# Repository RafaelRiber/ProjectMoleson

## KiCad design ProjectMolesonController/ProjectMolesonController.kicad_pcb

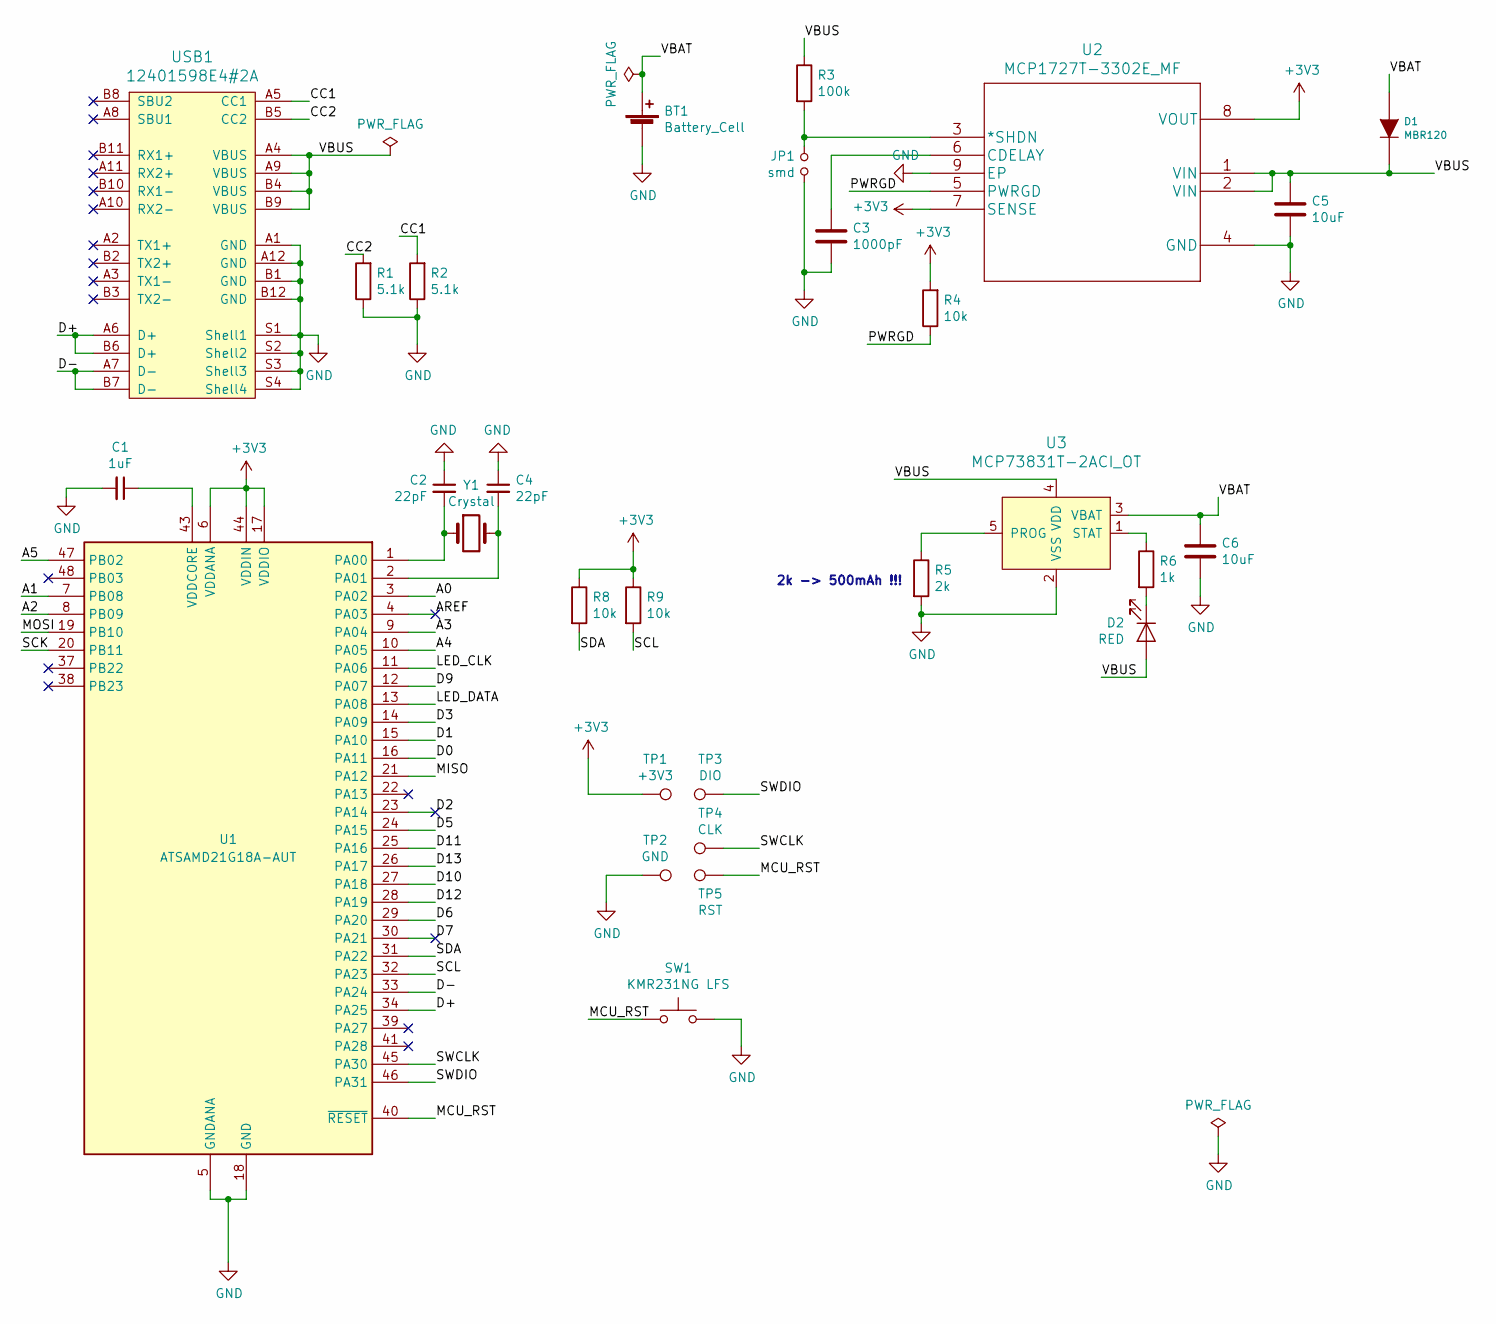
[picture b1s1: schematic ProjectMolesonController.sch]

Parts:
BT1: Battery_Cell; JST_PH_S2B-PH-SM4-TB_1x02-1MP_P2.00mm_Horizontal
C1: 1uF; C_0402_1005Metric
C2, C4: 22pF; C_0402_1005Metric
C3: 1000pF; C_0402_1005Metric
C5, C6: 10uF; C_0402_1005Metric
D1: MBR120; D_SOD-123F
D2: RED; LED_0805_2012Metric
JP1: smd; SolderJumper-2_P1.3mm_Open_RoundedPad1.0x1.5mm
R1, R2: 5.1k; R_0402_1005Metric
R3: 100k; R_0402_1005Metric
R4, R8, R9: 10k; R_0402_1005Metric
R5: 2k; R_0402_1005Metric
R6: 1k; R_0402_1005Metric
SW1: KMR231NG LFS; SW_Push_1P1T_NO_CK_KMR2
TP1: +3V3; TestPoint_Pad_D4.0mm
TP2: GND; TestPoint_Pad_D4.0mm
TP3: DIO; TestPoint_Pad_D4.0mm
TP4: CLK; TestPoint_Pad_D4.0mm
TP5: RST; TestPoint_Pad_D4.0mm
U1: ATSAMD21G18A-AUT; QFN50P700X700X90-49N
U2: MCP1727T-3302E_MF; DFN-8-1EP_3x3mm_P0.5mm_EP1.66x2.38mm
U3: MCP73831T-2ACI_OT; SOT-753; MPN MCP73831T-2ACI/OT; Digi-Key_PN MCP73831T-2ACI/OTCT-ND
USB1: 12401598E4#2A
Y1: Crystal; Crystal_SMD_3215-2Pin_3.2x1.5mm

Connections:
+3V3: R4.2, R8.1, R9.1, TP1.1, U1.6 (VDDANA), U1.17 (VDDIO), U1.36 (VDDIO), U1.44 (VDDIN), U2.7 (SENSE), U2.8 (VOUT)
/A0: U1.3 (PA02)
/A1: U1.7 (PB08)
/A2: U1.8 (PB09)
/A3: U1.9 (PA04)
/A4: U1.10 (PA05)
/A5: U1.47 (PB02)
/AREF: U1.4 (PA03)
/CC1: R2.2, USB1.A5 (CC1)
/CC2: R1.2, USB1.B5 (CC2)
/D0: U1.16 (PA11)
/D1: U1.15 (PA10)
/D2: U1.23 (PA14)
/D3: U1.14 (PA09)
/D5: U1.24 (PA15)
/D6: U1.29 (PA20)
/D7: U1.30 (PA21)
/D9: U1.12 (PA07)
/D10: U1.27 (PA18)
/D11: U1.25 (PA16)
/D12: U1.28 (PA19)
/D13: U1.26 (PA17)
/D+: U1.34 (PA25), USB1.A6 (D+), USB1.B6 (D+)
/D-: U1.33 (PA24), USB1.A7 (D-), USB1.B7 (D-)
/LED_CLK: U1.11 (PA06)
/LED_DATA: U1.13 (PA08)
/MCU_RST: SW1.1, TP5.1, U1.40 (~RESET)
/MISO: U1.21 (PA12)
/MOSI: U1.19 (PB10)
/PWRGD: R4.1, U2.5 (PWRGD)
/SCK: U1.20 (PB11)
/SCL: R9.2, U1.32 (PA23)
/SDA: R8.2, U1.31 (PA22)
/SWCLK: TP4.1, U1.45 (PA30)
/SWDIO: TP3.1, U1.46 (PA31)
/VBAT: BT1.1 (+), C6.1, D1.A, U3.3 (VBAT)
/VBUS: C5.1, D1.K, D2.2 (A), R3.1, U2.1 (VIN), U2.2 (VIN), U3.4 (VDD), USB1.A4 (VBUS), USB1.A9 (VBUS), USB1.B4 (VBUS), USB1.B9 (VBUS)
GND: BT1.2 (-), C1.2, C2.1, C3.2, C4.1, C5.2, C6.2, JP1.1, R1.1, R2.1, R5.2, SW1.2, TP2.1, U1.5 (GNDANA), U1.18 (GND), U1.35 (GND), U1.42 (GND), U2.4 (GND), U2.9 (EP), U3.2 (VSS), USB1.A1 (GND), USB1.A12 (GND), USB1.B1 (GND), USB1.B12 (GND), USB1.S1 (Shell1), USB1.S2 (Shell2), USB1.S3 (Shell3), USB1.S4 (Shell4)
unnamed: C1.1, U1.43 (VDDCORE)
unnamed: C2.2, U1.1 (PA00), Y1.1
unnamed: C3.1, U2.6 (CDELAY)
unnamed: C4.2, U1.2 (PA01), Y1.2
unnamed: D2.1 (K), R6.2
unnamed: JP1.2, R3.2, U2.3 (*SHDN)
unnamed: R5.1, U3.5 (PROG)
unnamed: R6.1, U3.1 (STAT)

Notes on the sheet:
2k -> 500mAh !!!

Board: 2 copper layers, 29 parts (0 on the bottom side), 22 nets, no tracks yet.

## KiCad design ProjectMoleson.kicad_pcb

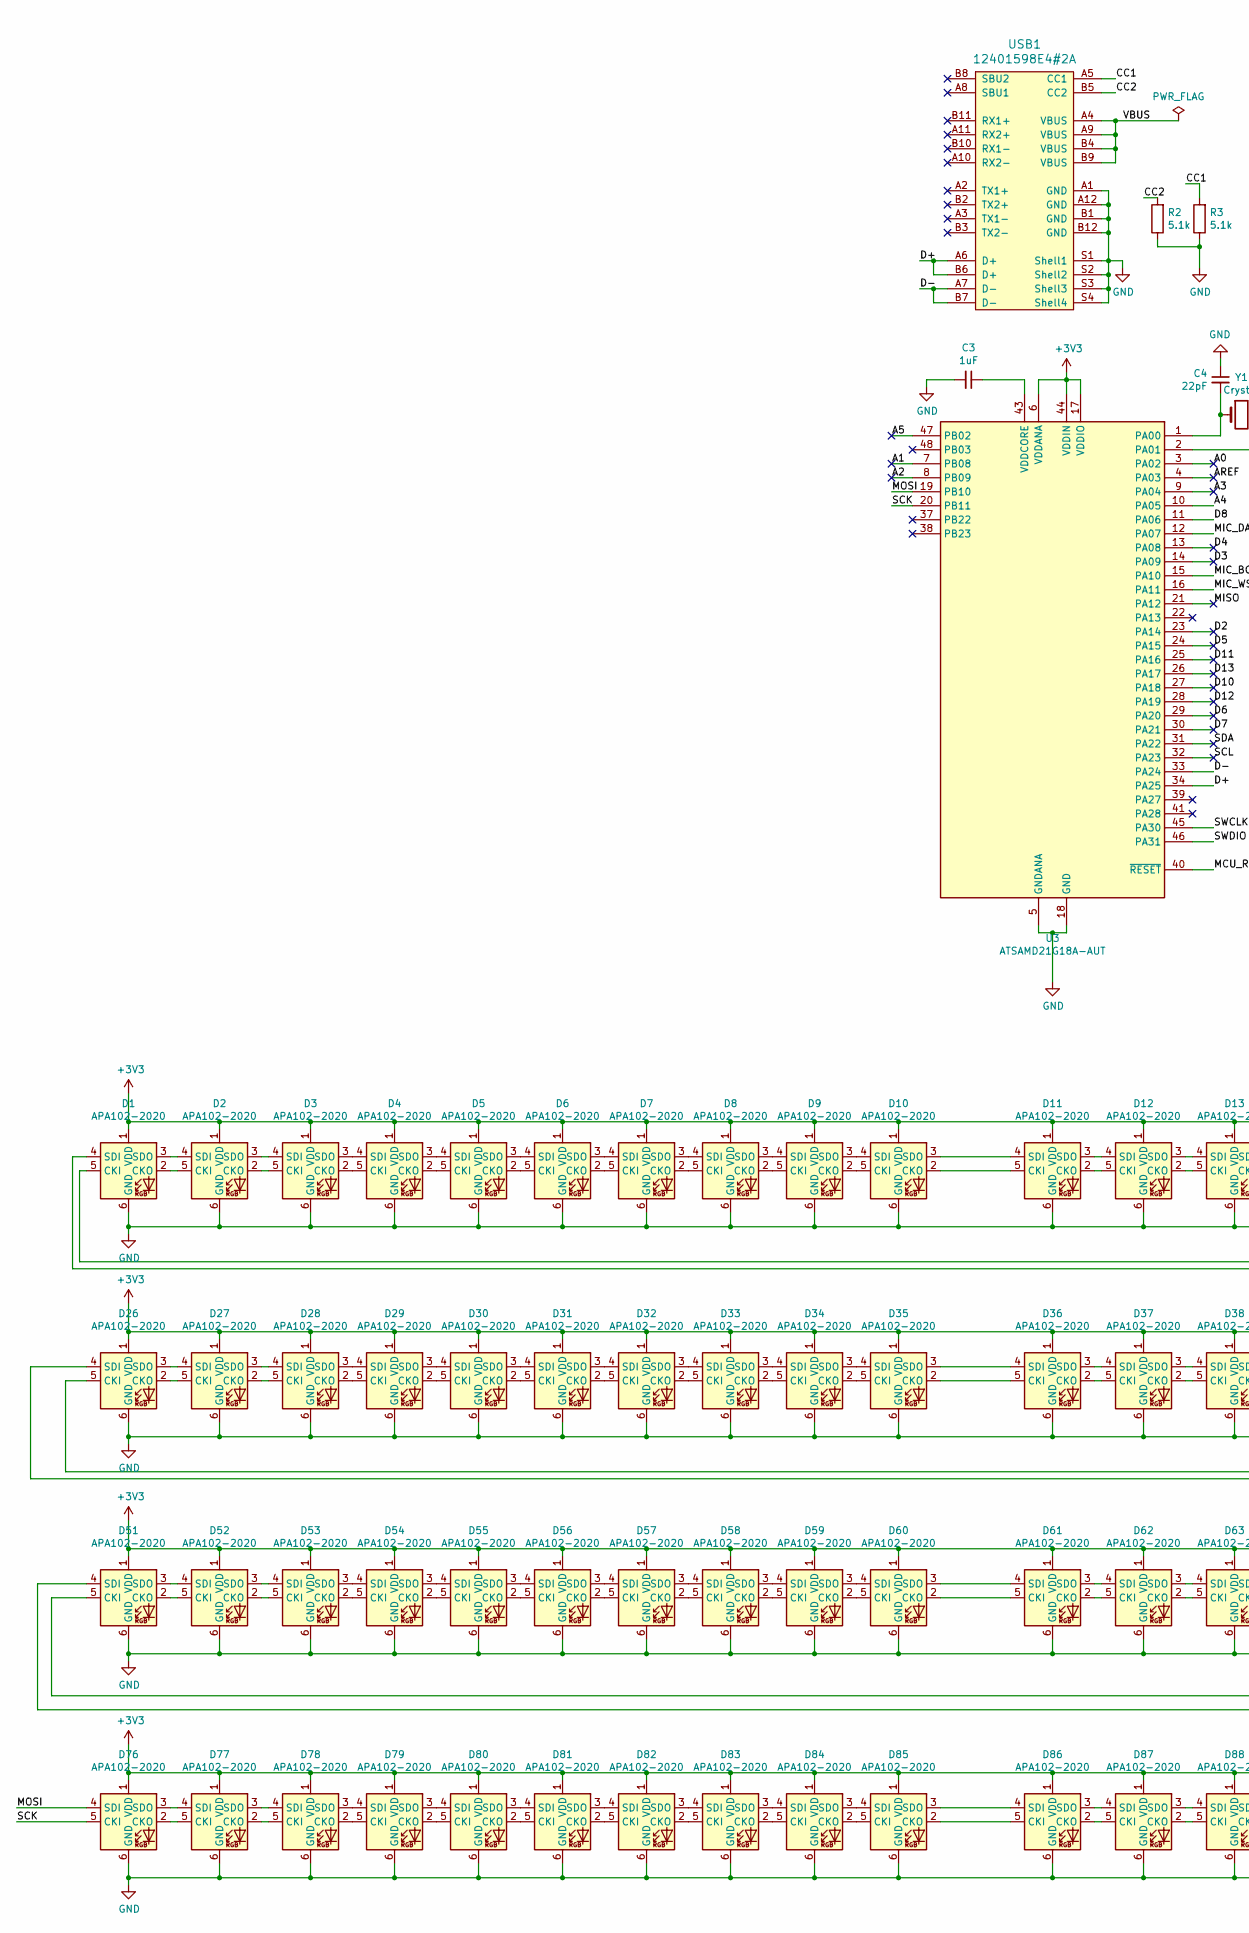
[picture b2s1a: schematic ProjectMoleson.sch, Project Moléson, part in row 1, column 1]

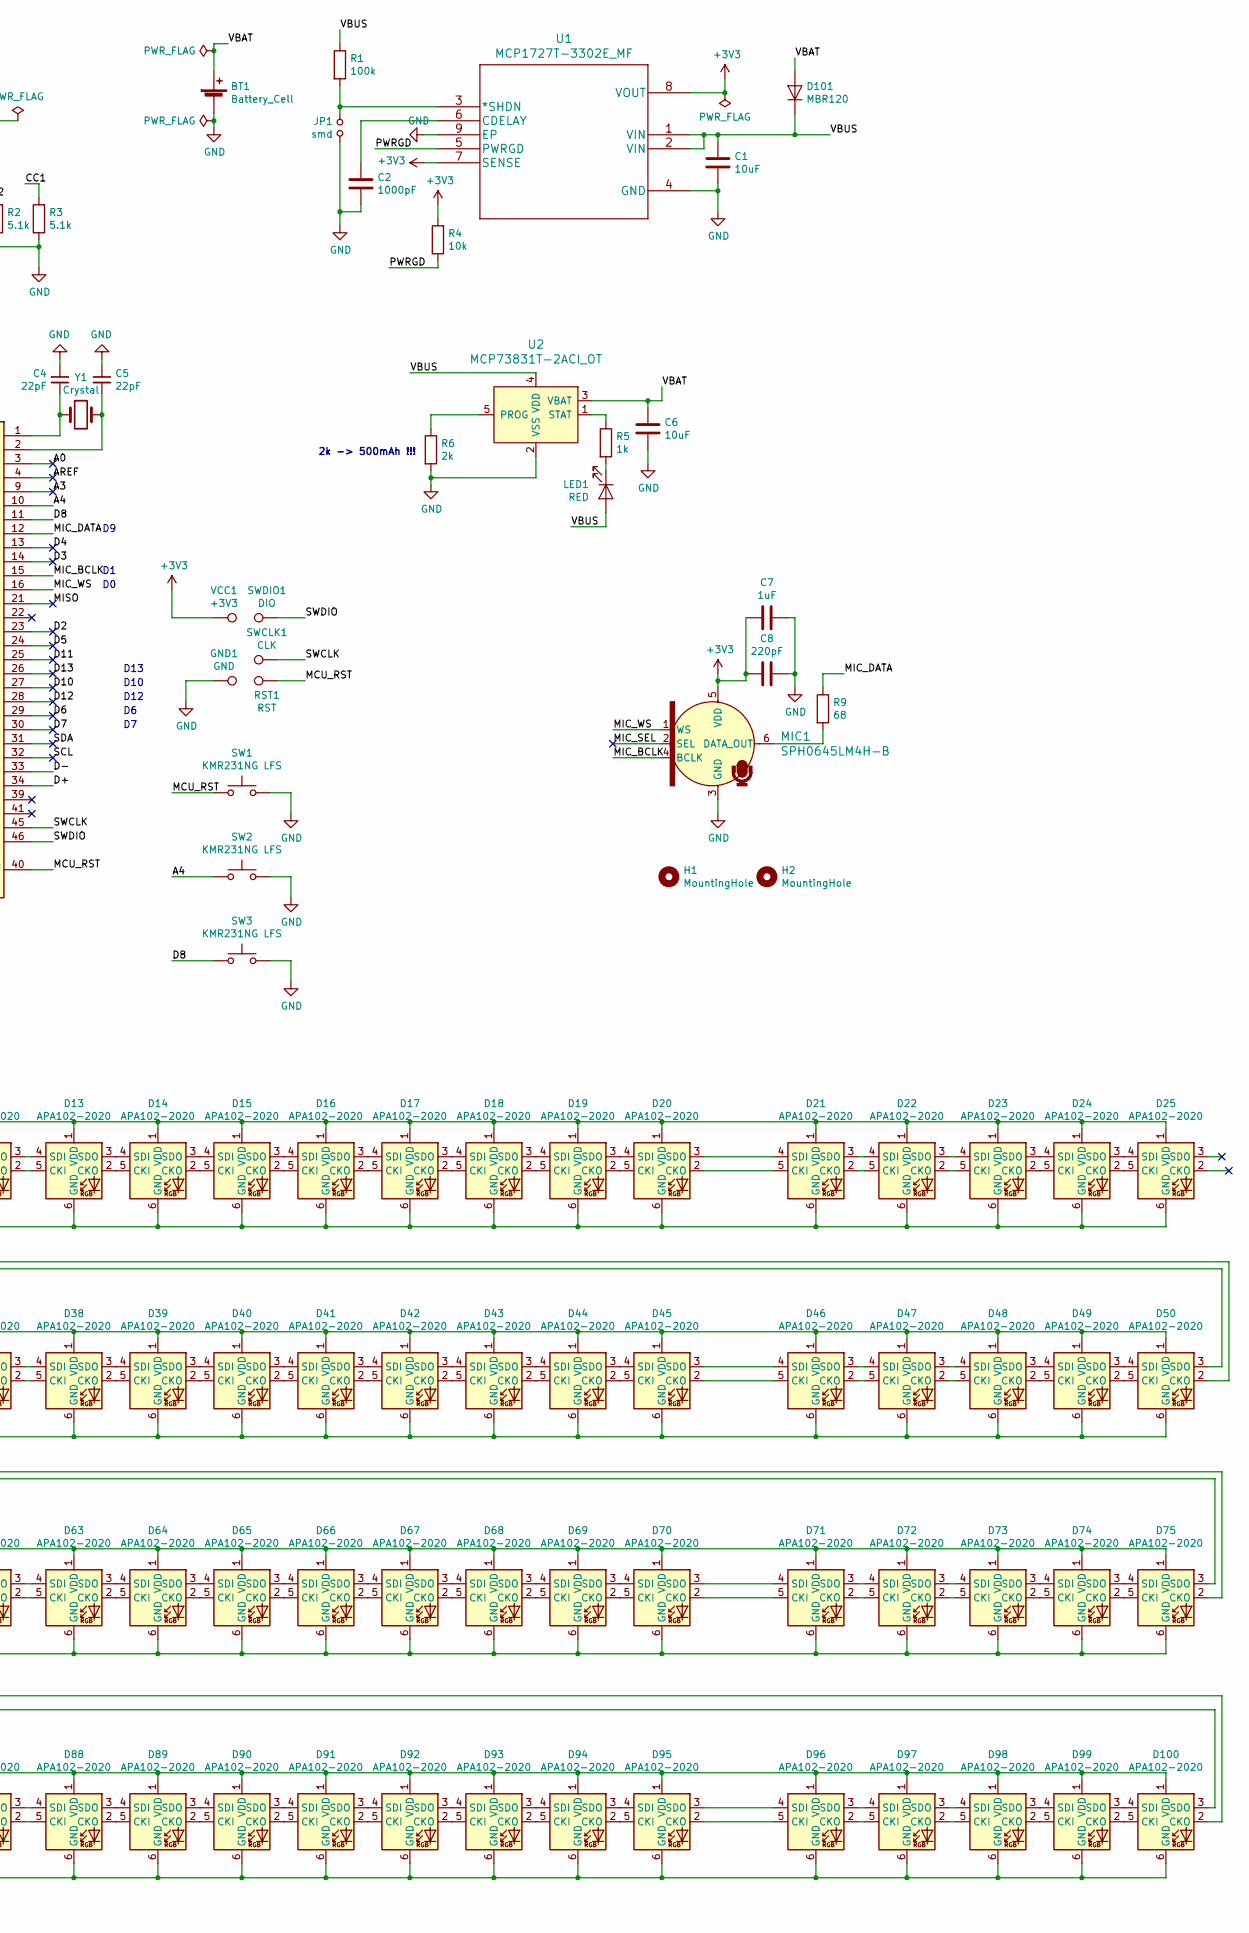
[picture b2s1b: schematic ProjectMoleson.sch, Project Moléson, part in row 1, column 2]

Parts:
BT1: Battery_Cell; JST_PH_S2B-PH-SM4-TB_1x02-1MP_P2.00mm_Horizontal
C1, C6: 10uF; C_0402_1005Metric
C2: 1000pF; C_0402_1005Metric
C3, C7: 1uF; C_0402_1005Metric
C4, C5: 22pF; C_0402_1005Metric
C8: 220pF; C_0402_1005Metric
D1, D2, D3, D4, D5, D6, D7, D8, D9, D10, D11, D12, D13, D14, D15, D16, D17, D18, D19, D20, D21, D22, D23, D24, D25, D26, D27, D28, D29, D30, D31, D32, D33, D34, D35, D36, D37, D38, D39, D40, D41, D42, D43, D44, D45, D46, D47, D48, D49, D50, D51, D52, D53, D54, D55, D56, D57, D58, D59, D60, D61, D62, D63, D64, D65, D66, D67, D68, D69, D70, D71, D72, D73, D74, D75, D76, D77, D78, D79, D80, D81, D82, D83, D84, D85, D86, D87, D88, D89, D90, D91, D92, D93, D94, D95, D96, D97, D98, D99, D100: APA102-2020; LED-APA102-2020
D101: MBR120; D_SOD-123F
GND1: GND; TestPoint_Pad_D4.0mm
H1, H2: MountingHole; MountingHole_4mm
JP1: smd; SolderJumper-2_P1.3mm_Open_RoundedPad1.0x1.5mm
LED1: RED; LED_0805_2012Metric
MIC1: SPH0645LM4H-B; MPN SPH0645LM4H-B; Digi-Key_PN 423-1405-1-ND
R1: 100k; R_0402_1005Metric
R2, R3: 5.1k; R_0402_1005Metric
R4: 10k; R_0402_1005Metric
R5: 1k; R_0402_1005Metric
R6: 2k; R_0402_1005Metric
R9: 68; R_0402_1005Metric
RST1: RST; TestPoint_Pad_D4.0mm
SW1, SW2, SW3: KMR231NG LFS; SW_Push_1P1T_NO_CK_KMR2
SWCLK1: CLK; TestPoint_Pad_D4.0mm
SWDIO1: DIO; TestPoint_Pad_D4.0mm
U1: MCP1727T-3302E_MF; DFN-8-1EP_3x3mm_P0.5mm_EP1.66x2.38mm
U2: MCP73831T-2ACI_OT; SOT-753; MPN MCP73831T-2ACI/OT; Digi-Key_PN MCP73831T-2ACI/OTCT-ND
U3: ATSAMD21G18A-AUT; QFN50P700X700X90-49N
USB1: 12401598E4#2A
VCC1: +3V3; TestPoint_Pad_D4.0mm
Y1: Crystal; Crystal_SMD_3215-2Pin_3.2x1.5mm

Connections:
+3V3: C7.2, C8.1, D1.1 (VDD), D2.1 (VDD), D3.1 (VDD), D4.1 (VDD), D5.1 (VDD), D6.1 (VDD), D7.1 (VDD), D8.1 (VDD), D9.1 (VDD), D10.1 (VDD), D11.1 (VDD), D12.1 (VDD), D13.1 (VDD), D14.1 (VDD), D15.1 (VDD), D16.1 (VDD), D17.1 (VDD), D18.1 (VDD), D19.1 (VDD), D20.1 (VDD), D21.1 (VDD), D22.1 (VDD), D23.1 (VDD), D24.1 (VDD), D25.1 (VDD), D26.1 (VDD), D27.1 (VDD), D28.1 (VDD), D29.1 (VDD), D30.1 (VDD), D31.1 (VDD), D32.1 (VDD), D33.1 (VDD), D34.1 (VDD), D35.1 (VDD), D36.1 (VDD), D37.1 (VDD), D38.1 (VDD), D39.1 (VDD), D40.1 (VDD), D41.1 (VDD), D42.1 (VDD), D43.1 (VDD), D44.1 (VDD), D45.1 (VDD), D46.1 (VDD), D47.1 (VDD), D48.1 (VDD), D49.1 (VDD), D50.1 (VDD), D51.1 (VDD), D52.1 (VDD), D53.1 (VDD), D54.1 (VDD), D55.1 (VDD), D56.1 (VDD), D57.1 (VDD), D58.1 (VDD), D59.1 (VDD), D60.1 (VDD), D61.1 (VDD), D62.1 (VDD), D63.1 (VDD), D64.1 (VDD), D65.1 (VDD), D66.1 (VDD), D67.1 (VDD), D68.1 (VDD), D69.1 (VDD), D70.1 (VDD), D71.1 (VDD), D72.1 (VDD), D73.1 (VDD), D74.1 (VDD), D75.1 (VDD), D76.1 (VDD), D77.1 (VDD), D78.1 (VDD), D79.1 (VDD), D80.1 (VDD), D81.1 (VDD), D82.1 (VDD), D83.1 (VDD), D84.1 (VDD), D85.1 (VDD), D86.1 (VDD), D87.1 (VDD), D88.1 (VDD), D89.1 (VDD), D90.1 (VDD), D91.1 (VDD), D92.1 (VDD), D93.1 (VDD), D94.1 (VDD), D95.1 (VDD), D96.1 (VDD), D97.1 (VDD), D98.1 (VDD), D99.1 (VDD), D100.1 (VDD), MIC1.5 (VDD), R4.2, U1.7 (SENSE), U1.8 (VOUT), U3.6 (VDDANA), U3.17 (VDDIO), U3.36 (VDDIO), U3.44 (VDDIN), VCC1.1
/A0: U3.3 (PA02)
/A1: U3.7 (PB08)
/A2: U3.8 (PB09)
/A3: U3.9 (PA04)
/A4: SW2.1, U3.10 (PA05)
/A5: U3.47 (PB02)
/AREF: U3.4 (PA03)
/CC1: R3.2, USB1.A5 (CC1)
/CC2: R2.2, USB1.B5 (CC2)
/D2: U3.23 (PA14)
/D3: U3.14 (PA09)
/D4: U3.13 (PA08)
/D5: U3.24 (PA15)
/D6: U3.29 (PA20)
/D7: U3.30 (PA21)
/D8: SW3.1, U3.11 (PA06)
/D10: U3.27 (PA18)
/D11: U3.25 (PA16)
/D12: U3.28 (PA19)
/D13: U3.26 (PA17)
/D+: U3.34 (PA25), USB1.A6 (D+), USB1.B6 (D+)
/D-: U3.33 (PA24), USB1.A7 (D-), USB1.B7 (D-)
/MCU_RST: RST1.1, SW1.1, U3.40 (~RESET)
/MIC_BCLK: MIC1.4 (BCLK), U3.15 (PA10)
/MIC_DATA: R9.1, U3.12 (PA07)
/MIC_SEL: MIC1.2 (SEL)
/MIC_WS: MIC1.1 (WS), U3.16 (PA11)
/MISO: U3.21 (PA12)
/MOSI: D76.4 (SDI), U3.19 (PB10)
/PWRGD: R4.1, U1.5 (PWRGD)
/SCK: D76.5 (CKI), U3.20 (PB11)
/SCL: U3.32 (PA23)
/SDA: U3.31 (PA22)
/SWCLK: SWCLK1.1, U3.45 (PA30)
/SWDIO: SWDIO1.1, U3.46 (PA31)
/VBAT: BT1.1 (+), C6.1, D101.2 (A), U2.3 (VBAT)
/VBUS: C1.1, D101.1 (K), LED1.2 (A), R1.1, U1.1 (VIN), U1.2 (VIN), U2.4 (VDD), USB1.A4 (VBUS), USB1.A9 (VBUS), USB1.B4 (VBUS), USB1.B9 (VBUS)
GND: BT1.2 (-), C1.2, C2.2, C3.2, C4.1, C5.1, C6.2, C7.1, C8.2, D1.6 (GND), D2.6 (GND), D3.6 (GND), D4.6 (GND), D5.6 (GND), D6.6 (GND), D7.6 (GND), D8.6 (GND), D9.6 (GND), D10.6 (GND), D11.6 (GND), D12.6 (GND), D13.6 (GND), D14.6 (GND), D15.6 (GND), D16.6 (GND), D17.6 (GND), D18.6 (GND), D19.6 (GND), D20.6 (GND), D21.6 (GND), D22.6 (GND), D23.6 (GND), D24.6 (GND), D25.6 (GND), D26.6 (GND), D27.6 (GND), D28.6 (GND), D29.6 (GND), D30.6 (GND), D31.6 (GND), D32.6 (GND), D33.6 (GND), D34.6 (GND), D35.6 (GND), D36.6 (GND), D37.6 (GND), D38.6 (GND), D39.6 (GND), D40.6 (GND), D41.6 (GND), D42.6 (GND), D43.6 (GND), D44.6 (GND), D45.6 (GND), D46.6 (GND), D47.6 (GND), D48.6 (GND), D49.6 (GND), D50.6 (GND), D51.6 (GND), D52.6 (GND), D53.6 (GND), D54.6 (GND), D55.6 (GND), D56.6 (GND), D57.6 (GND), D58.6 (GND), D59.6 (GND), D60.6 (GND), D61.6 (GND), D62.6 (GND), D63.6 (GND), D64.6 (GND), D65.6 (GND), D66.6 (GND), D67.6 (GND), D68.6 (GND), D69.6 (GND), D70.6 (GND), D71.6 (GND), D72.6 (GND), D73.6 (GND), D74.6 (GND), D75.6 (GND), D76.6 (GND), D77.6 (GND), D78.6 (GND), D79.6 (GND), D80.6 (GND), D81.6 (GND), D82.6 (GND), D83.6 (GND), D84.6 (GND), D85.6 (GND), D86.6 (GND), D87.6 (GND), D88.6 (GND), D89.6 (GND), D90.6 (GND), D91.6 (GND), D92.6 (GND), D93.6 (GND), D94.6 (GND), D95.6 (GND), D96.6 (GND), D97.6 (GND), D98.6 (GND), D99.6 (GND), D100.6 (GND), GND1.1, JP1.1, MIC1.3 (GND), R2.1, R3.1, R6.2, SW1.2, SW2.2, SW3.2, U1.4 (GND), U1.9 (EP), U2.2 (VSS), U3.5 (GNDANA), U3.18 (GND), U3.35 (GND), U3.42 (GND), USB1.A1 (GND), USB1.A12 (GND), USB1.B1 (GND), USB1.B12 (GND), USB1.S1 (Shell1), USB1.S2 (Shell2), USB1.S3 (Shell3), USB1.S4 (Shell4)
unnamed: C2.1, U1.6 (CDELAY)
unnamed: C3.1, U3.43 (VDDCORE)
unnamed: C4.2, U3.1 (PA00), Y1.1
unnamed: C5.2, U3.2 (PA01), Y1.2
unnamed: D1.2 (CKO), D2.5 (CKI)
unnamed: D1.3 (SDO), D2.4 (SDI)
unnamed: D1.4 (SDI), D50.3 (SDO)
unnamed: D1.5 (CKI), D50.2 (CKO)
unnamed: D2.2 (CKO), D3.5 (CKI)
unnamed: D2.3 (SDO), D3.4 (SDI)
unnamed: D3.2 (CKO), D4.5 (CKI)
unnamed: D3.3 (SDO), D4.4 (SDI)
unnamed: D4.2 (CKO), D5.5 (CKI)
unnamed: D4.3 (SDO), D5.4 (SDI)
unnamed: D5.2 (CKO), D6.5 (CKI)
unnamed: D5.3 (SDO), D6.4 (SDI)
unnamed: D6.2 (CKO), D7.5 (CKI)
unnamed: D6.3 (SDO), D7.4 (SDI)
unnamed: D7.2 (CKO), D8.5 (CKI)
unnamed: D7.3 (SDO), D8.4 (SDI)
unnamed: D8.2 (CKO), D9.5 (CKI)
unnamed: D8.3 (SDO), D9.4 (SDI)
unnamed: D10.2 (CKO), D11.5 (CKI)
unnamed: D10.3 (SDO), D11.4 (SDI)
unnamed: D9.3 (SDO), D10.4 (SDI)
unnamed: D9.2 (CKO), D10.5 (CKI)
unnamed: D11.2 (CKO), D12.5 (CKI)
unnamed: D11.3 (SDO), D12.4 (SDI)
unnamed: D12.2 (CKO), D13.5 (CKI)
unnamed: D12.3 (SDO), D13.4 (SDI)
unnamed: D13.2 (CKO), D14.5 (CKI)
unnamed: D13.3 (SDO), D14.4 (SDI)
unnamed: D14.2 (CKO), D15.5 (CKI)
unnamed: D14.3 (SDO), D15.4 (SDI)
unnamed: D15.2 (CKO), D16.5 (CKI)
unnamed: D15.3 (SDO), D16.4 (SDI)
unnamed: D16.2 (CKO), D17.5 (CKI)
unnamed: D16.3 (SDO), D17.4 (SDI)
unnamed: D17.2 (CKO), D18.5 (CKI)
unnamed: D17.3 (SDO), D18.4 (SDI)
unnamed: D18.2 (CKO), D19.5 (CKI)
unnamed: D18.3 (SDO), D19.4 (SDI)
unnamed: D19.2 (CKO), D20.5 (CKI)
unnamed: D19.3 (SDO), D20.4 (SDI)
unnamed: D20.2 (CKO), D21.5 (CKI)
unnamed: D20.3 (SDO), D21.4 (SDI)
unnamed: D21.2 (CKO), D22.5 (CKI)
unnamed: D21.3 (SDO), D22.4 (SDI)
unnamed: D22.2 (CKO), D23.5 (CKI)
unnamed: D22.3 (SDO), D23.4 (SDI)
unnamed: D23.2 (CKO), D24.5 (CKI)
unnamed: D23.3 (SDO), D24.4 (SDI)
unnamed: D24.2 (CKO), D25.5 (CKI)
unnamed: D24.3 (SDO), D25.4 (SDI)
unnamed: D26.2 (CKO), D27.5 (CKI)
unnamed: D26.3 (SDO), D27.4 (SDI)
unnamed: D26.4 (SDI), D75.3 (SDO)
unnamed: D26.5 (CKI), D75.2 (CKO)
unnamed: D27.2 (CKO), D28.5 (CKI)
unnamed: D27.3 (SDO), D28.4 (SDI)
unnamed: D28.2 (CKO), D29.5 (CKI)
unnamed: D28.3 (SDO), D29.4 (SDI)
unnamed: D29.2 (CKO), D30.5 (CKI)
unnamed: D29.3 (SDO), D30.4 (SDI)
unnamed: D30.2 (CKO), D31.5 (CKI)
unnamed: D30.3 (SDO), D31.4 (SDI)
unnamed: D31.2 (CKO), D32.5 (CKI)
unnamed: D31.3 (SDO), D32.4 (SDI)
unnamed: D32.2 (CKO), D33.5 (CKI)
unnamed: D32.3 (SDO), D33.4 (SDI)
unnamed: D33.2 (CKO), D34.5 (CKI)
unnamed: D33.3 (SDO), D34.4 (SDI)
unnamed: D34.2 (CKO), D35.5 (CKI)
unnamed: D34.3 (SDO), D35.4 (SDI)
unnamed: D35.2 (CKO), D36.5 (CKI)
unnamed: D35.3 (SDO), D36.4 (SDI)
unnamed: D36.2 (CKO), D37.5 (CKI)
unnamed: D36.3 (SDO), D37.4 (SDI)
unnamed: D37.2 (CKO), D38.5 (CKI)
unnamed: D37.3 (SDO), D38.4 (SDI)
unnamed: D38.2 (CKO), D39.5 (CKI)
unnamed: D38.3 (SDO), D39.4 (SDI)
unnamed: D39.2 (CKO), D40.5 (CKI)
unnamed: D39.3 (SDO), D40.4 (SDI)
unnamed: D40.2 (CKO), D41.5 (CKI)
unnamed: D40.3 (SDO), D41.4 (SDI)
unnamed: D41.2 (CKO), D42.5 (CKI)
unnamed: D41.3 (SDO), D42.4 (SDI)
unnamed: D42.2 (CKO), D43.5 (CKI)
unnamed: D42.3 (SDO), D43.4 (SDI)
unnamed: D43.2 (CKO), D44.5 (CKI)
unnamed: D43.3 (SDO), D44.4 (SDI)
unnamed: D44.2 (CKO), D45.5 (CKI)
unnamed: D44.3 (SDO), D45.4 (SDI)
unnamed: D45.2 (CKO), D46.5 (CKI)
unnamed: D45.3 (SDO), D46.4 (SDI)
unnamed: D46.2 (CKO), D47.5 (CKI)
unnamed: D46.3 (SDO), D47.4 (SDI)
unnamed: D47.2 (CKO), D48.5 (CKI)
unnamed: D47.3 (SDO), D48.4 (SDI)
unnamed: D48.2 (CKO), D49.5 (CKI)
unnamed: D48.3 (SDO), D49.4 (SDI)
unnamed: D49.2 (CKO), D50.5 (CKI)
unnamed: D49.3 (SDO), D50.4 (SDI)
unnamed: D51.2 (CKO), D52.5 (CKI)
unnamed: D51.3 (SDO), D52.4 (SDI)
unnamed: D52.2 (CKO), D53.5 (CKI)
unnamed: D52.3 (SDO), D53.4 (SDI)
unnamed: D53.2 (CKO), D54.5 (CKI)
unnamed: D53.3 (SDO), D54.4 (SDI)
unnamed: D54.2 (CKO), D55.5 (CKI)
unnamed: D54.3 (SDO), D55.4 (SDI)
unnamed: D55.2 (CKO), D56.5 (CKI)
unnamed: D55.3 (SDO), D56.4 (SDI)
unnamed: D56.2 (CKO), D57.5 (CKI)
unnamed: D56.3 (SDO), D57.4 (SDI)
unnamed: D57.2 (CKO), D58.5 (CKI)
unnamed: D57.3 (SDO), D58.4 (SDI)
unnamed: D58.2 (CKO), D59.5 (CKI)
unnamed: D58.3 (SDO), D59.4 (SDI)
unnamed: D59.2 (CKO), D60.5 (CKI)
unnamed: D59.3 (SDO), D60.4 (SDI)
unnamed: D60.2 (CKO), D61.5 (CKI)
unnamed: D60.3 (SDO), D61.4 (SDI)
unnamed: D61.2 (CKO), D62.5 (CKI)
unnamed: D61.3 (SDO), D62.4 (SDI)
unnamed: D62.2 (CKO), D63.5 (CKI)
unnamed: D62.3 (SDO), D63.4 (SDI)
unnamed: D63.2 (CKO), D64.5 (CKI)
unnamed: D63.3 (SDO), D64.4 (SDI)
unnamed: D64.2 (CKO), D65.5 (CKI)
unnamed: D64.3 (SDO), D65.4 (SDI)
unnamed: D65.2 (CKO), D66.5 (CKI)
unnamed: D65.3 (SDO), D66.4 (SDI)
unnamed: D66.2 (CKO), D67.5 (CKI)
unnamed: D66.3 (SDO), D67.4 (SDI)
unnamed: D67.2 (CKO), D68.5 (CKI)
unnamed: D67.3 (SDO), D68.4 (SDI)
unnamed: D68.2 (CKO), D69.5 (CKI)
unnamed: D68.3 (SDO), D69.4 (SDI)
unnamed: D69.2 (CKO), D70.5 (CKI)
unnamed: D69.3 (SDO), D70.4 (SDI)
unnamed: D70.2 (CKO), D71.5 (CKI)
unnamed: D70.3 (SDO), D71.4 (SDI)
unnamed: D71.2 (CKO), D72.5 (CKI)
unnamed: D71.3 (SDO), D72.4 (SDI)
unnamed: D72.2 (CKO), D73.5 (CKI)
unnamed: D72.3 (SDO), D73.4 (SDI)
unnamed: D73.2 (CKO), D74.5 (CKI)
unnamed: D73.3 (SDO), D74.4 (SDI)
unnamed: D74.2 (CKO), D75.5 (CKI)
unnamed: D74.3 (SDO), D75.4 (SDI)
unnamed: D76.2 (CKO), D77.5 (CKI)
unnamed: D76.3 (SDO), D77.4 (SDI)
unnamed: D77.2 (CKO), D78.5 (CKI)
unnamed: D77.3 (SDO), D78.4 (SDI)
unnamed: D78.2 (CKO), D79.5 (CKI)
unnamed: D78.3 (SDO), D79.4 (SDI)
unnamed: D79.2 (CKO), D80.5 (CKI)
unnamed: D79.3 (SDO), D80.4 (SDI)
unnamed: D80.2 (CKO), D81.5 (CKI)
unnamed: D80.3 (SDO), D81.4 (SDI)
unnamed: D81.2 (CKO), D82.5 (CKI)
unnamed: D81.3 (SDO), D82.4 (SDI)
unnamed: D82.2 (CKO), D83.5 (CKI)
unnamed: D82.3 (SDO), D83.4 (SDI)
unnamed: D83.2 (CKO), D84.5 (CKI)
unnamed: D83.3 (SDO), D84.4 (SDI)
unnamed: D84.2 (CKO), D85.5 (CKI)
unnamed: D84.3 (SDO), D85.4 (SDI)
unnamed: D85.2 (CKO), D86.5 (CKI)
unnamed: D85.3 (SDO), D86.4 (SDI)
unnamed: D86.2 (CKO), D87.5 (CKI)
unnamed: D86.3 (SDO), D87.4 (SDI)
unnamed: D87.2 (CKO), D88.5 (CKI)
unnamed: D87.3 (SDO), D88.4 (SDI)
unnamed: D88.2 (CKO), D89.5 (CKI)
unnamed: D88.3 (SDO), D89.4 (SDI)
unnamed: D89.2 (CKO), D90.5 (CKI)
unnamed: D89.3 (SDO), D90.4 (SDI)
unnamed: D90.2 (CKO), D91.5 (CKI)
unnamed: D90.3 (SDO), D91.4 (SDI)
unnamed: D91.2 (CKO), D92.5 (CKI)
unnamed: D91.3 (SDO), D92.4 (SDI)
unnamed: D92.2 (CKO), D93.5 (CKI)
unnamed: D92.3 (SDO), D93.4 (SDI)
unnamed: D93.2 (CKO), D94.5 (CKI)
unnamed: D93.3 (SDO), D94.4 (SDI)
unnamed: D94.2 (CKO), D95.5 (CKI)
unnamed: D94.3 (SDO), D95.4 (SDI)
unnamed: D95.2 (CKO), D96.5 (CKI)
unnamed: D95.3 (SDO), D96.4 (SDI)
unnamed: D96.2 (CKO), D97.5 (CKI)
unnamed: D96.3 (SDO), D97.4 (SDI)
unnamed: D97.2 (CKO), D98.5 (CKI)
unnamed: D97.3 (SDO), D98.4 (SDI)
unnamed: D98.2 (CKO), D99.5 (CKI)
unnamed: D98.3 (SDO), D99.4 (SDI)
unnamed: D51.5 (CKI), D100.2 (CKO)
unnamed: D51.4 (SDI), D100.3 (SDO)
unnamed: D99.3 (SDO), D100.4 (SDI)
unnamed: D99.2 (CKO), D100.5 (CKI)
unnamed: JP1.2, R1.2, U1.3 (*SHDN)
unnamed: LED1.1 (K), R5.2
unnamed: MIC1.6 (DATA_OUT), R9.2
unnamed: R5.1, U2.1 (STAT)
unnamed: R6.1, U2.5 (PROG)

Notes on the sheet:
2k -> 500mAh !!!
D12
D10
D13

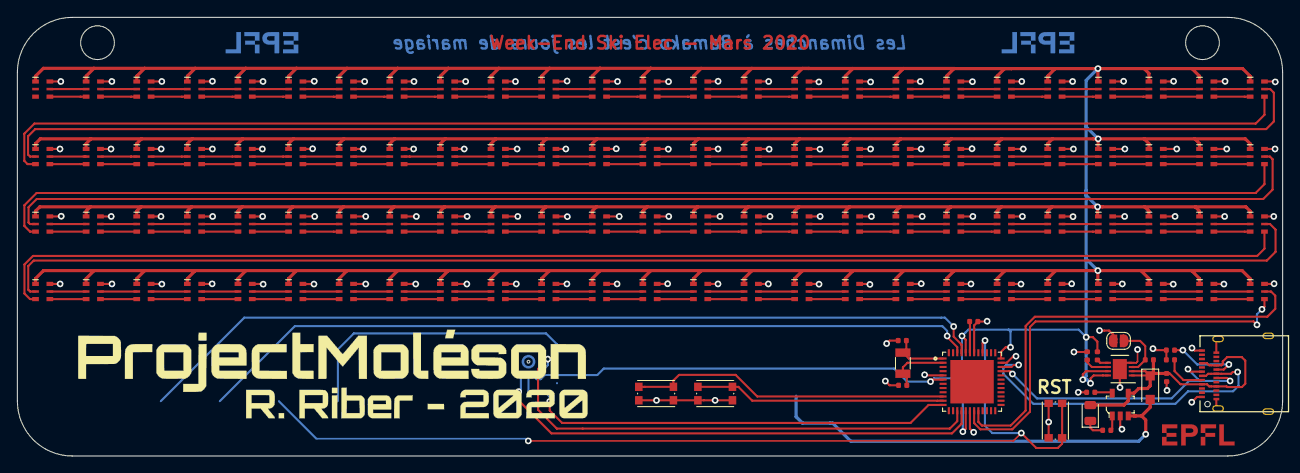
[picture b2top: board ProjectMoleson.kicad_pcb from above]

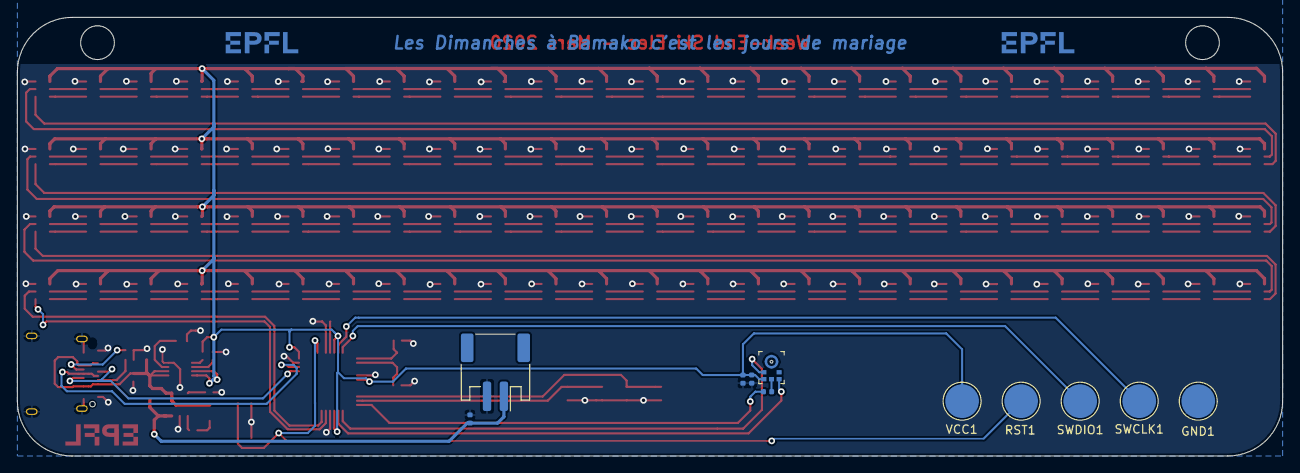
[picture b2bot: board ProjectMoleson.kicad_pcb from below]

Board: 2 copper layers, 150.0 x 52.0 mm, 135 parts (11 on the bottom side), 226 nets.
